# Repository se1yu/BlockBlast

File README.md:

# BlockBlast! 
- Demo Link: https://youtu.be/8z5zvf6NJ1U?si=ciNaijVOC2jGjhIF

Using knowledge from ECE 319H at UT Austin (Intro to Embedded Systems) to build a custom video game console and to program Block Blast from scratch. 

Block Blast is a puzzle game I implemented for a MSPM0G3507 microcontroller, displayed on a 128×160 ST7735 Liquid Crystal Display (LCD) screen. The player is presented with an 8×8 grid and a tray of three randomly selected blocks. Using a joystick and four external buttons, the player picks up blocks from the tray, moves them around the grid, and drops them into position. When an entire row or column of the grid becomes filled, it clears and the player earns points. The game ends when any remaining block in the tray has no valid position anywhere on the board. The game supports English and Spanish, tracks a persistent high score across rounds, and features four distinct sound effects triggered by gameplay events.
# Images

--------

# System Architecture
There are two ISRs running concurrently:
Armed with TimerG12_IntArm(80000000/30, 2), which fires an interrupt every 30ms. It does three things each tick:
- Calls JoyStick_In(&JoyX, &JoyY) — which internally triggers ADC_InDual (analog-to-digital-convertor) on ADC1 channels 4 and 6 (PB17 and PB19), sampling both joystick axes simultaneously via a dual-channel 12-bit ADC conversion. According to the Nyquist Theorem, an input should be sampled at a frequency at least twice the maximum input frequency. 30Hz (30 times a second) sampling is well above the maximum frequency a human wrist can move a joystick!
- Calls Switch_In() — reads the four external buttons wired to PA24–PA27, returning a 4-bit value where each bit represents one directional button that is currently being pressed (right/down/left/up). 
- Stores results in the global variables JoyX, JoyY, and sw_status for the main program to access these external hardware updates.

Regarding Audio, we have the SysTick_Handler — Audio DAC at 11 kHz:
Armed with SysTick_IntArm(80000000/11000, 0), this fires every ~90µs and drives the 5-bit binary-weighted DAC on PB0–PB4. It maintains three global variables: pointer to sound array(values to be played to output sound), arrayCount (total # of bytes per sound array), and arrayIndex (current position). Each tick it outputs pointer[arrayIndex] to DAC5_Out() and increments the index. When the array is exhausted it disables the interrupt. Sound is started by calling Sound_Start(pt, count) which resets the index and re-enables the interrupt. This ISR runs at higher priority (0) than the game timer (2) so audio never stutters during gameplay.

# ADC & Joystick
JoyStick_Init() calls ADC_InitDual(ADC1, 4, 6, ADCVREF_VDDA), configuring ADC1 to sequentially sample two channels in one software trigger: channel 4 (PB17, horizontal) and channel 6 (PB19, vertical). ADC_InDual triggers the conversion and "busy-waits" for both results, returning values 0–4095 for each axis. The neutral position is approximately 2048. In Game_Tick, the bounding numbers of 1000 and 3000 define deflection zones — below 1000 means pushed one way, above 3000 means the other. The joystick counts as two slide potentiometers sampled periodically by the ADC at 30 Hz inside the timer ISR.

# Switches/Buttons
Switch_Init() configures PA24–PA27 as digital inputs with PINCM = 0x40081 (input enable + pull-up). Switch_In() reads GPIOA->DIN31_0, masks bits 24–27, and right-shifts by 24 to produce a clean 4-bit value. These are four external buttons wired:
- Bit 0 = right (select / confirm)
- Bit 1 = down (place block)
- Bit 2 = left (back / cancel, requires ~1 second hold on game screen to go backwards)
- Bit 3 = up (pick up block / cancel pickup)

# Sound
Four gameplay sounds are defined in sounds.h as const uint8_t arrays of 5-bit DAC samples recorded at 11 kHz:
- Block_Pickup() — plays when the player picks up a block from the tray
- Block_Place() — plays on successful block placement
- Block_Reject() — plays when a drop is attempted in an invalid position
- Block_Clear() — plays when one or more rows or columns are cleared
Each calls Sound_Start(array, count) which loads the pointer/counter globals and enables the SysTick interrupt. The DAC is a 5-bit R-2R ladder on PB0–PB4, giving 32 voltage levels from 0 to 3.3V.

# Sprites & Graphics
All sprites I drew in Microsoft Paint are stored as const uint16_t arrays in images.h in RGB565 format (16 bit). ST7735_DrawBitmap(x, y, ptr, w, h) renders them with y as the bottom pixel edge. The active sprites in gameplay are:
- Home (128×160) — the menu/title screen background
- grid (128×160) — the full game screen including the 8×8 grid and tray area background
- single (12×12) — 1×1 cell
- miniwide (24×12) — 2×1 cells
- minitall (12×24) — 1×2 cells
- minisquare (24×24) — 2×2 cells
- wide (36×12) — 3×1 cells
- tall (12×36) — 1×3 cells
- square (36×36) — 3×3 cells
Moving sprite: The held block moves across the grid in 12px increments (one cell) responding to joystick deflection. On each move, ST7735_DrawBitmap(grid) redraws the background, all filled cells are repainted as solid 10×10px colored squares inside each 12×12 cell, the tray is redrawn, and finally the held block is drawn at its new position.

# Grid & Game Logic
The grid state is a uint8_t grid_matrix[8][8] where 0 = empty and 1 = filled. Block types are described by a BlockType_t struct containing the sprite pointer, pixel dimensions, and cell footprint. The active tray is traySlotType[3] — indices into allBlockTypes[7] — randomized each respawn using a linear congruential generator from SysTick->VAL at game start for true randomness. Random32() implements a linear congruential generator: M = 1664525*M + 1013904223. RandomType() uses (Random32() >> 24) % 7 — taking bits 31–24 for a cycle length of 2²⁴ rather than the short-cycling low bits. The seed M = SysTick->VAL is set once at Game_Init(), capturing the hardware counter at the moment the player starts the game, ensuring a different block sequence every round.

The canPlace(slot, col, row) checks bounds and scans the footprint against the matrix. stampBlock writes 1s into the matrix. checkAndClearLines() after every placement scans all 8 rows and 8 columns, marks full ones, then zeroes any cell whose row or column was full — handling intersections correctly without double-counting. isGameOver() iterates all available tray blocks and calls canBlockFitAnywhere() which scans every valid grid position; if any available block has zero valid placements, the game ends.

# LEDs 
Three LEDs on PA15–PA17 indicate which tray slot is currently selected. LED_On(data) left-shifts data by 15 to align with the GPIO pins. Only the LED corresponding to traySelection lights up, and it goes dark when that slot's block is picked up or placed.

# Language Support 
All user-facing strings exist in both English and Spanish. A lang variable (0 = English, 1 = Spanish) indexes into parallel string arrays for menu labels, tutorial text, and prompts. The language cycles with the Language menu option and persists through the game session.

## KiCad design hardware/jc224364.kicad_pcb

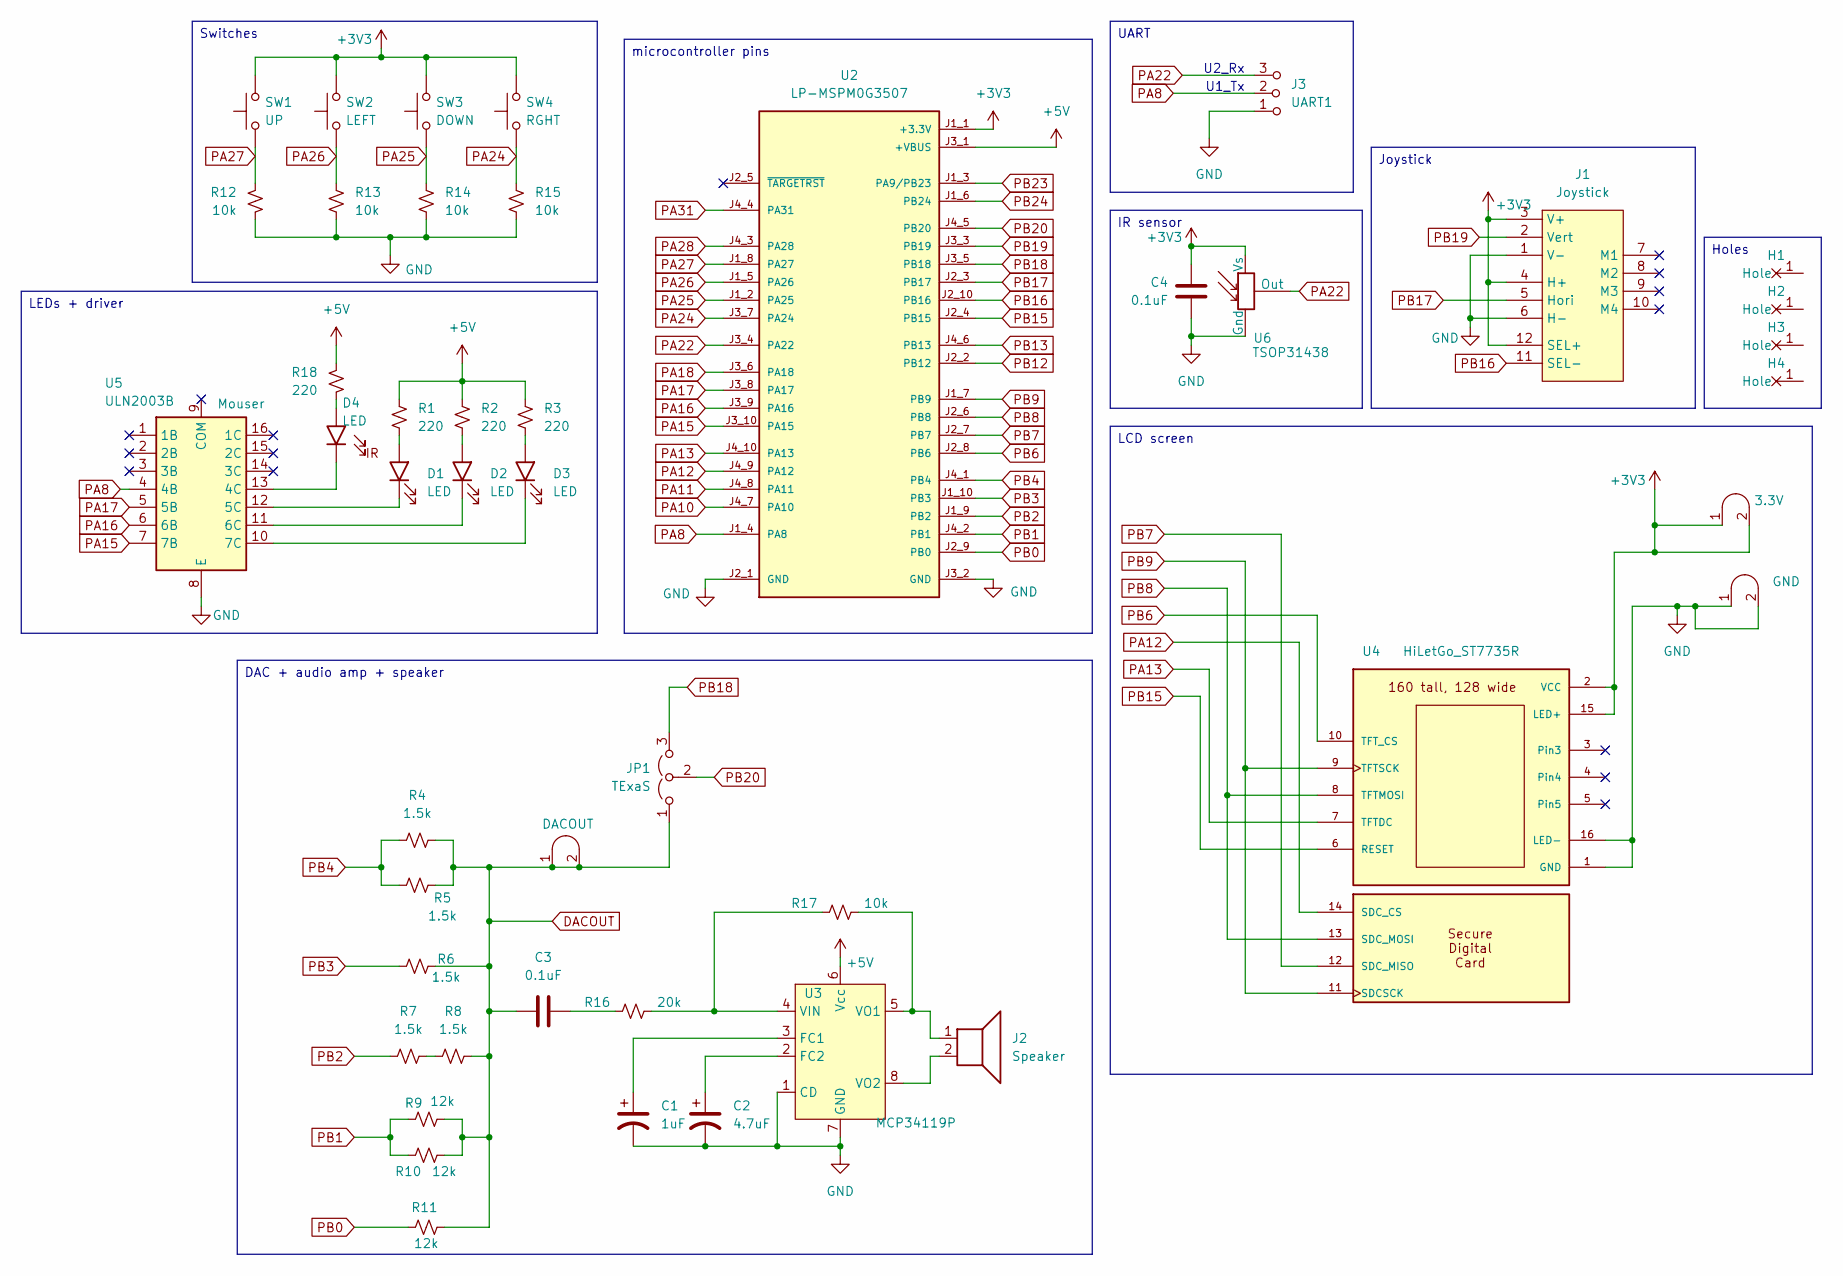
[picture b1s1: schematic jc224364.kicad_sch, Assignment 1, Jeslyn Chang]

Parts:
C1: 1uF; CP_Radial_Tantal200mil
C2: 4.7uF; CP_Radial_Tantal200mil
C3, C4: 0.1uF; C_Axial_200mil
D1, D2, D3, D4: LED; LED_D5.0mm
H1, H2, H3, H4: MountingHole_4_40
J1: Joystick; SparkfunJoystick
J2: Speaker; PinHeader_1x02_P2.54mm_Vertical
J3: UART1; PinHeader_1x03_P2.54mm_Vertical
J6: GND; Testpoint_1x02_P2.54mm
J7: DACOUT; Testpoint_1x02_P2.54mm
JP1: TExaS; PinHeader_1x03_P2.54mm_Vertical
R1, R2, R3, R18: 220; R_Axial_DIN0204_L3.6mm_D1.6mm_P7.62mm_Horizontal
R4, R5, R6, R7, R8: 1.5k; R_Axial_DIN0204_L3.6mm_D1.6mm_P7.62mm_Horizontal
R9, R10, R11: 12k; R_Axial_DIN0204_L3.6mm_D1.6mm_P7.62mm_Horizontal
R12, R13, R14, R15, R17: 10k; R_Axial_DIN0204_L3.6mm_D1.6mm_P7.62mm_Horizontal
R16: 20k; R_Axial_DIN0204_L3.6mm_D1.6mm_P7.62mm_Horizontal
SW1: UP; SW_PUSH_6mm
SW2: LEFT; SW_PUSH_6mm
SW3: DOWN; SW_PUSH_6mm
SW4: RGHT; SW_PUSH_6mm
TP1: 3.3V; Testpoint_1x02_P2.54mm
U2: LP-MSPM0G3507; ti_LP_MSPM0G3507
U3: MCP34119P; DIP-8_W7.62mm_LongPads
U4: HiLetGo_ST7735R; hiletgo_st7735r
U5: ULN2003B; DIP-16_W7.62mm
U6: TSOP31438

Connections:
+3V3: C4.1, J1.3 (V+), J1.4 (H+), J1.12 (SEL+), SW1.2, SW2.2, SW3.2, SW4.2, TP1.1 (A), TP1.2 (B), U2.J1_1 (+3.3V), U4.2 (VCC), U4.15 (LED+), U6.2 (Vs)
+5V: R1.1, R2.1, R3.1, R18.1, U2.J3_1 (+VBUS), U3.6 (Vcc)
DACOUT: C3.1, J7.1 (A), J7.2 (B), JP1.1 (A), R4.1, R5.1, R6.1, R8.1, R9.1, R10.1, R11.1
GND: C1.2, C2.2, C4.2, J1.1 (V-), J1.6 (H-), J3.1 (A), J6.1 (A), J6.2 (B), R12.2, R13.2, R14.2, R15.2, U2.J2_1 (GND), U2.J3_2 (GND), U3.1 (CD), U3.7 (GND), U4.1 (GND), U4.16 (LED-), U5.8 (E), U6.1 (Gnd)
unnamed: C3.2, R16.2
unnamed: D1.2 (A), R1.2
unnamed: D1.1 (K), U5.12 (5C)
unnamed: D2.2 (A), R2.2
unnamed: D2.1 (K), U5.11 (6C)
unnamed: D3.2 (A), R3.2
unnamed: D3.1 (K), U5.10 (7C)
unnamed: D4.2 (A), R18.2
unnamed: D4.1 (K), U5.13 (4C)
unnamed: R7.1, R8.2
unnamed: C1.1, U3.3 (FC1)
unnamed: C2.1, U3.2 (FC2)
unnamed: R16.1, R17.2, U3.4 (VIN)
unnamed: J2.1, R17.1, U3.5 (VO1)
unnamed: J2.2, U3.8 (VO2)
PA8: J3.2 (B), U2.J1_4 (PA8), U5.4 (4B)
PA10: U2.J4_7 (PA10)
PA11: U2.J4_8 (PA11)
PA12: U2.J4_9 (PA12), U4.14 (SDC_CS)
PA13: U2.J4_10 (PA13), U4.7 (TFTDC)
PA15: U2.J3_10 (PA15), U5.7 (7B)
PA16: U2.J3_9 (PA16), U5.6 (6B)
PA17: U2.J3_8 (PA17), U5.5 (5B)
PA18: U2.J3_6 (PA18)
PA22: J3.3 (C), U2.J3_4 (PA22), U6.3 (Out)
PA24: R15.1, SW4.1, U2.J3_7 (PA24)
PA25: R14.1, SW3.1, U2.J1_2 (PA25)
PA26: R13.1, SW2.1, U2.J1_5 (PA26)
PA27: R12.1, SW1.1, U2.J1_8 (PA27)
PA28: U2.J4_3 (PA28)
PA31: U2.J4_4 (PA31)
PB0: R11.2, U2.J2_9 (PB0)
PB1: R9.2, R10.2, U2.J4_2 (PB1)
PB2: R7.2, U2.J1_9 (PB2)
PB3: R6.2, U2.J1_10 (PB3)
PB4: R4.2, R5.2, U2.J4_1 (PB4)
PB6: U2.J2_8 (PB6), U4.10 (TFT_CS)
PB7: U2.J2_7 (PB7), U4.12 (SDC_MISO)
PB8: U2.J2_6 (PB8), U4.8 (TFTMOSI), U4.13 (SDC_MOSI)
PB9: U2.J1_7 (PB9), U4.9 (TFTSCK), U4.11 (SDCSCK)
PB12: U2.J2_2 (PB12)
PB13: U2.J4_6 (PB13)
PB15: U2.J2_4 (PB15), U4.6 (RESET)
PB16: J1.11 (SEL-), U2.J2_10 (PB16)
PB17: J1.5 (Hori), U2.J2_3 (PB17)
PB18: JP1.3 (B), U2.J3_5 (PB18)
PB19: J1.2 (Vert), U2.J3_3 (PB19)
PB20: JP1.2 (C), U2.J4_5 (PB20)
PB23: U2.J1_3 (PA9/PB23)
PB24: U2.J1_6 (PB24)

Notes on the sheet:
U2_Rx
U1_Tx
Joystick
Holes
LEDs + driver
IR sensor
microcontroller pins
LCD screen
DAC + audio amp + speaker
Switches
UART

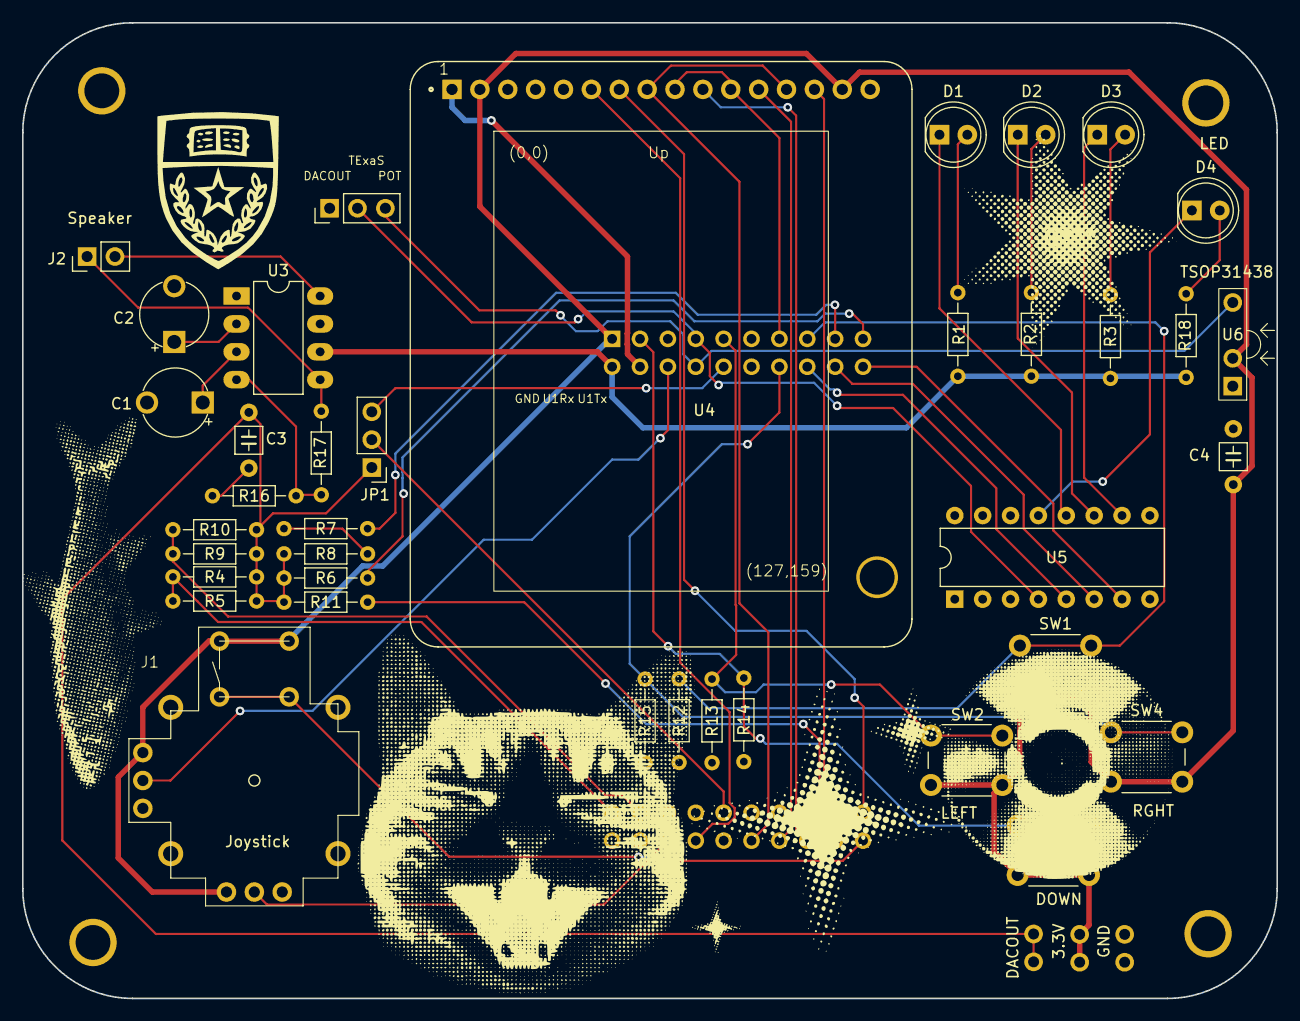
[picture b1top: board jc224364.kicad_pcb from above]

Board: 2 copper layers, 114.3 x 88.9 mm, 46 parts (1 on the bottom side), 45 nets.

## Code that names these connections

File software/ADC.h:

/*!
 * @defgroup ADC
 * @brief Analog to digital conversion
  <table>
<caption id="ADCpins">ADC pins on the MSPM0G3507</caption>
<tr><th>Pin  <th>ADC channel<th>Sensor
<tr><td>PA27 <td>ADC0 channel 0 <td>J1.8 also MKII light interrupt
<tr><td>PA26 <td>ADC0 channel 1 <td>J1.6 MKII microphone in
<tr><td>PA25 <td>ADC0 channel 2 <td>J1.2 MKII Joystick X
<tr><td>PA24 <td>ADC0 channel 3 <td>J3.27 ***free***
<tr><td>PB25 <td>ADC0 channel 4 <td>J19.7 (insert 0ohm R74, no U3 OPA2365)
<tr><td>PB24 <td>ADC0 channel 5 <td>J1.5 thermistor, also MKII joystick select button
<tr><td>PB20 <td>ADC0 channel 6 <td>J4.36 ***free***
<tr><td>PA22 <td>ADC0 channel 7 <td>J24 MKII Accelerometer Y

<tr><td>PA15 <td>ADC1 channel 0 <td>J3.30 (also DACout)
<tr><td>PA16 <td>ADC1 channel 1 <td>J3.29 ***free***
<tr><td>PA17 <td>ADC1 channel 2 <td>J3.28 ***free***
<tr><td>PA18 <td>ADC1 channel 3 <td>J3.26 MKII Joystick Y
<tr><td>PB17 <td>ADC1 channel 4 <td>J2.18 ***free***
<tr><td>PB18 <td>ADC1 channel 5 <td>J3.25 MKII Accelerometer Z
<tr><td>PB19 <td>ADC1 channel 6 <td>J3.23 MKII Accelerometer X
<tr><td>PA21 <td>ADC1 channel 7 <td>J17.8 (insert R20, remove R3)

</table>
 * @{*/
/**
 * @file      ADC.h
 * @brief     Initialize 12-bit ADC0 and/or ADC1
 * @details   ADC input, software trigger, 12-bit conversion<br>
 * The ADC allows two possible references: 2.5V or 3.3V.<br>
 * The internal 2.5V reference is lower noise, but limits the range to 0 to 2.5V.<br>
 * The other possibility is to use the analog voltage supply at 3.3V,
 * making the ADC range 0 to 3.3V. In this driver, the 3.3V range is selected.
 * There are several configurations (each with initialization and a
 * read ADC with software trigger, busy-wait function)<br>

 * @version   ECE319K v1.0
 * @author    Daniel Valvano and Jonathan Valvano
 * @copyright Copyright 2023 by Jonathan W. Valvano, valvano@mail.utexas.edu,
 * @warning   AS-IS
 * @note      For more information see  http://users.ece.utexas.edu/~valvano/
 * @date      August 13, 2023
 <table>
<caption id="ADCpins2">ADC pins on the MSPM0G3507</caption>
<tr><th>Pin  <th>ADC channel<th>Sensor
<tr><td>PA27 <td>ADC0 channel 0 <td>J1.8 also MKII light interrupt
<tr><td>PA26 <td>ADC0 channel 1 <td>J1.6 MKII microphone in
<tr><td>PA25 <td>ADC0 channel 2 <td>J1.2 MKII Joystick X
<tr><td>PA24 <td>ADC0 channel 3 <td>J3.27 ***free***
<tr><td>PB25 <td>ADC0 channel 4 <td>J19.7 (insert 0ohm R74, no U3 OPA2365)
<tr><td>PB24 <td>ADC0 channel 5 <td>J1.5 also MKII joystick select button
<tr><td>PB20 <td>ADC0 channel 6 <td>J4.36 ***free***
<tr><td>PA22 <td>ADC0 channel 7 <td>J24 MKII Accelerometer Y

<tr><td>PA15 <td>ADC1 channel 0 <td>J3.30 (also DACout)
<tr><td>PA16 <td>ADC1 channel 1 <td>J3.29 ***free***
<tr><td>PA17 <td>ADC1 channel 2 <td>J3.28 ***free***
<tr><td>PA18 <td>ADC1 channel 3 <td>J3.26 MKII Joystick Y
<tr><td>PB17 <td>ADC1 channel 4 <td>J2.18 ***free***
<tr><td>PB18 <td>ADC1 channel 5 <td>J3.25 MKII Accelerometer Z
<tr><td>PB19 <td>ADC1 channel 6 <td>J3.23 MKII Accelerometer X
<tr><td>PA21 <td>ADC1 channel 7 <td>J17.8 (insert R20, remove R3)

</table>
  ****note to students****<br>
  the data sheet says the ADC does not work when clock is 80 MHz
  however, the ADC seems to work on my boards at 80 MHz
  I suggest you try 80MHz, but if it doesn't work, switch to 40MHz
  ******************************************************************************/



//#ifndef __ADC_H__
//#define __ADC_H__
#include <ti/devices/msp/msp.h>
#include <stdint.h>
/**
 * \brief using ADCVREF_INT means choose internal 2.5V reference for accuracy
 */
#define ADCVREF_INT  0x200
/**
 * \brief using ADCVREF_EXT means choose external reference not tested
 */ 
#define ADCVREF_EXT  0x100
/**
 * \brief using ADCVREF_VDDA means choose power line 3.3V reference for 0 to 3.3V range
 */
#define ADCVREF_VDDA 0x000

/**
 * Initialize 12-bit ADC0 in software-triggered mode to take
 * measurements when the associated function is called.
 * One channel is to be measured
 * @param channel is the 0 to 7
 * @param reference is ADCVREF_INT, ADCVREF_EXT, ADCVREF_VDDA
 * @return none 
 * @brief  Initialize 12-bit ADC0
 */
void ADC0_Init(uint32_t channel, uint32_t reference);

/**
 * Trigger a single ADC0 measurement,
 * wait for it to complete, and return the 12-bit result
 * as 0 to 4095.
 * The ADC input voltage range is 0 to 3.3V.
 * Busy-wait synchronization used.
 * @param none
 * @return 12-bit result
 * @note  Assumes ADC0_Init has been called.
 * @brief  Trigger ADC measurement and wait for result.
 */
uint32_t ADC0_In(void);

/**
 * Initialize 12-bit ADC1 in software-triggered mode to take
 * measurements when the associated function is called.
 * One channel is to be measured
 * @param channel is the 0 to 7
 * @param reference is ADCVREF_INT, ADCVREF_EXT, ADCVREF_VDDA
 * @return none 
 * @brief  Initialize 12-bit ADC0
 */
void ADC1_Init(uint32_t channel, uint32_t reference);

/**
 * Trigger a single ADC1 measurement,
 * wait for it to complete, and return the 12-bit result
 * as 0 to 4095.
 * The ADC input voltage range is 0 to 3.3V.
 * Busy-wait synchronization used.
 * @param none
 * @return 12-bit result
 * @note  Assumes ADC1_Init has been called.
 * @brief  Trigger ADC measurement and wait for result.
 */
uint32_t ADC1_In(void);

/**
 * Initialize 12-bit ADC0 or ADC1 in software-triggered mode to take
 * measurements when the associated function is called.
 * One channel is to be measured
 * @param adc12 is ADC0 or ADC1
 * @param channel is the 0 to 7
 * @param reference is ADCVREF_INT, ADCVREF_EXT, ADCVREF_VDDA
 * @return none
 * @brief  Initialize 12-bit ADC0
 */
void ADC_Init(ADC12_Regs *adc12, uint32_t channel, uint32_t reference);

/**
 * Trigger a single ADC0 or ADC1 measurement,
 * wait for it to complete, and return the 12-bit result
 * as 0 to 4095.
 * The ADC input voltage range is 0 to 3.3V.
 * Busy-wait synchronization used.
 * @param adc12 is ADC0 or ADC1
 * @return 12-bit result
 * @note  Assumes ADC_Init has been called.
 * @brief  Trigger ADC measurement and wait for result.
 */
uint32_t ADC_In(ADC12_Regs *adc12);

/**
 * Initialize 12-bit ADC0 or ADC1 in software-triggered mode to take
 * measurements when the associated function is called.
 * Two channels are to be measured
 * @param adc12 is ADC0 or ADC1
 * @param channel1 is the 0 to 7
 * @param channel2 is the 0 to 7
 * @param reference is ADCVREF_INT, ADCVREF_EXT, ADCVREF_VDDA
 * @return none 
 * @brief  Initialize 12-bit ADC for two channels
 */
void ADC_InitDual(ADC12_Regs *adc12, uint32_t channel1, uint32_t channel2, uint32_t reference);

/**
 * Trigger a dual ADC0 or ADC1 measurement,
 * wait for it to complete, and return the two 12-bit results
 * as 0 to 4095.
 * The ADC input voltage range is 0 to 3.3V.
 * Busy-wait synchronization used.
 * @param adc12 is ADC0 or ADC1
 * @param *d1 address into which the first ADC sample will be stored
 * @param *d2 address into which the second ADC sample will be stored
 * @return none 
 * @note  Assumes ADC_InitDual has been called.
 * @brief  Trigger two ADC measurements and wait for results.
 */
void ADC_InDual(ADC12_Regs *adc12, uint32_t *d1, uint32_t *d2);

/**
 * Initialize 12-bit ADC0 or ADC1 in software-triggered mode to take
 * measurements when the associated function is called.
 * three channels are to be measured
 * @param adc12 is ADC0 or ADC1
 * @param channel1 is the 0 to 7
 * @param channel2 is the 0 to 7
 * @param channel3 is the 0 to 7
 * @param reference is ADCVREF_INT, ADCVREF_EXT, ADCVREF_VDDA
 * @return none
 * @brief  Initialize 12-bit ADC for three channels
 */
void ADC_InitTriple(ADC12_Regs *adc12,uint32_t channel1,uint32_t channel2,uint32_t channel3,uint32_t reference);

/**
 * Trigger a triple ADC0 or ADC1 measurement,
 * wait for it to complete, and return the three 12-bit results
 * as 0 to 4095.
 * The ADC input voltage range is 0 to 3.3V.
 * Busy-wait synchronization used.
 * @param adc12 is ADC0 or ADC1
 * @param *d1 address into which the first ADC sample will be stored
 * @param *d2 address into which the second ADC sample will be stored
 * @param *d3 address into which the third ADC sample will be stored
 * @return none
 * @note  Assumes ADC_InitTriple has been called.
 * @brief  Trigger three ADC measurements and wait for results.
 */
void ADC_InTriple(ADC12_Regs *adc12,uint32_t *d1, uint32_t *d2, uint32_t *d3);

/**
 * Initialize 12-bit ADC0 in software-triggered mode to take
 * measurements when the associated function is called.
 * One channel is to be measured 2^n times in average.
 * @param channel is the 0 to 7
 * @param n 0 to 7
 * @return none 
 * @brief  Initialize 12-bit ADC0 for hardware averaging
 * @note uses ADCVREF_VDDA, so range is 0 to 3.3V
 */
void ADC0_InitAve(uint32_t channel, uint32_t n);

//#endif //  __ADC_H__
/** @}*/

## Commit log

2026-04-02 Hardware files
2026-04-16 default software file added
2026-04-22 updated readME
    Expanded the README to include detailed game mechanics, system architecture, joystick and button functionality, sound implementation, graphics handling, game logic, LED indicators, and language suppo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
2026-04-22 added files for software
2026-04-22 Add images to README for Block Blast
    Added images to the README to enhance visual representation of Block Blast.
2026-04-22 Enhance README with title and demo link
    Updated project title and added demo link to README.
